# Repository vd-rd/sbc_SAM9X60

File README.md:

# Microchip SAM9X60 SBC

This board embeds a SIP (single core 600MHz ARM926 with 1Gb DDR2) with ACT8945a PMIC, IO headers and microSD/eMMC storage.

Board overview (draft):
[TBD]

## Board features
| Characteristic | Description |
| --- | --- |
| Dimensions | 60mm x 40mm |
| Processor | Microchip SAM9X60 @600MHz |
| Oscillators | 32.768kHz slow clock, 24MHz main clock |
| RAM | 128MB embedded DDR2 memory |
| Storage | microSD/eMMC |
| USB | 1 microUSB client |
| Ethernet | 2 10/100M RMII with pins on header |
| WiFi | 1 SDIO adapter with wifi/bt combo |
| Supply | Power path between USB/Vin/Battery, 5V max |

## Notes and observations
[TBD]

## Resources

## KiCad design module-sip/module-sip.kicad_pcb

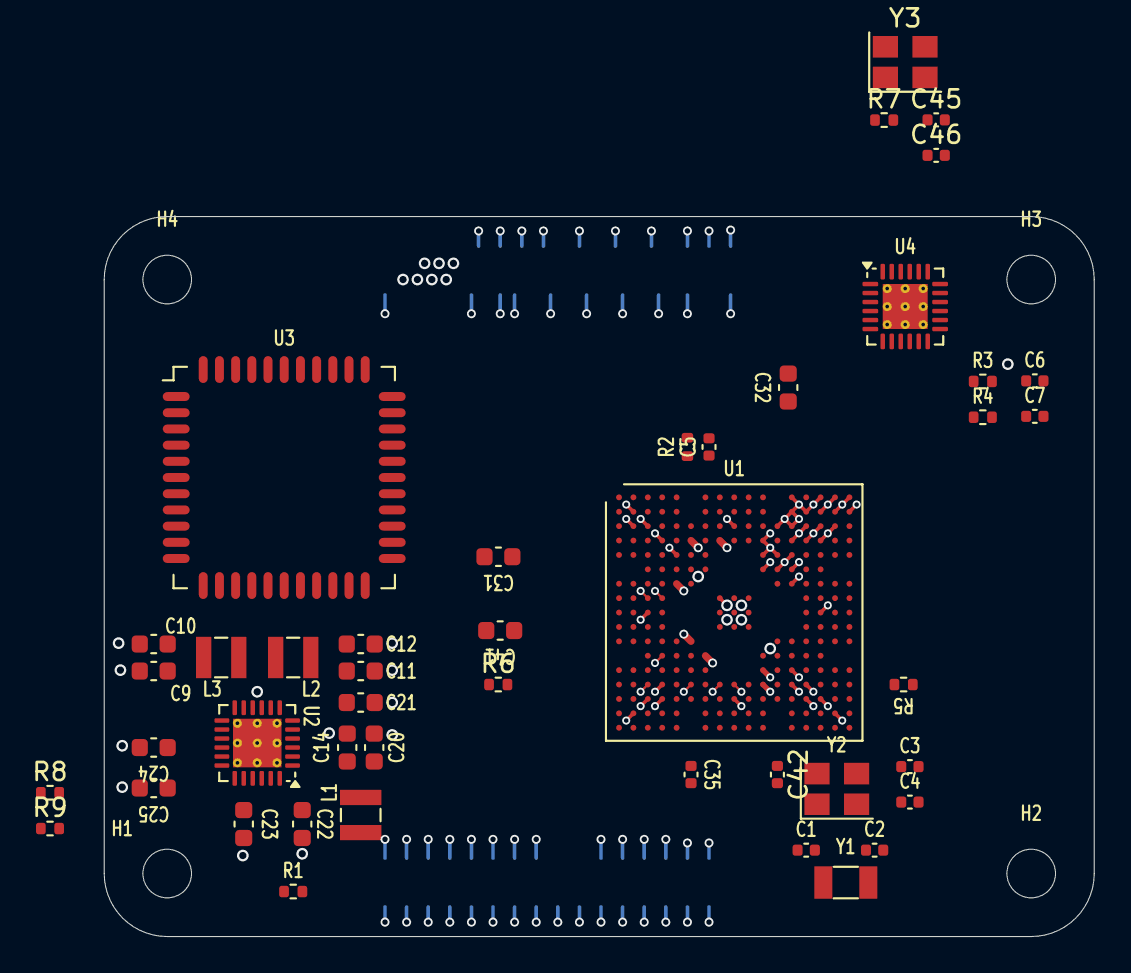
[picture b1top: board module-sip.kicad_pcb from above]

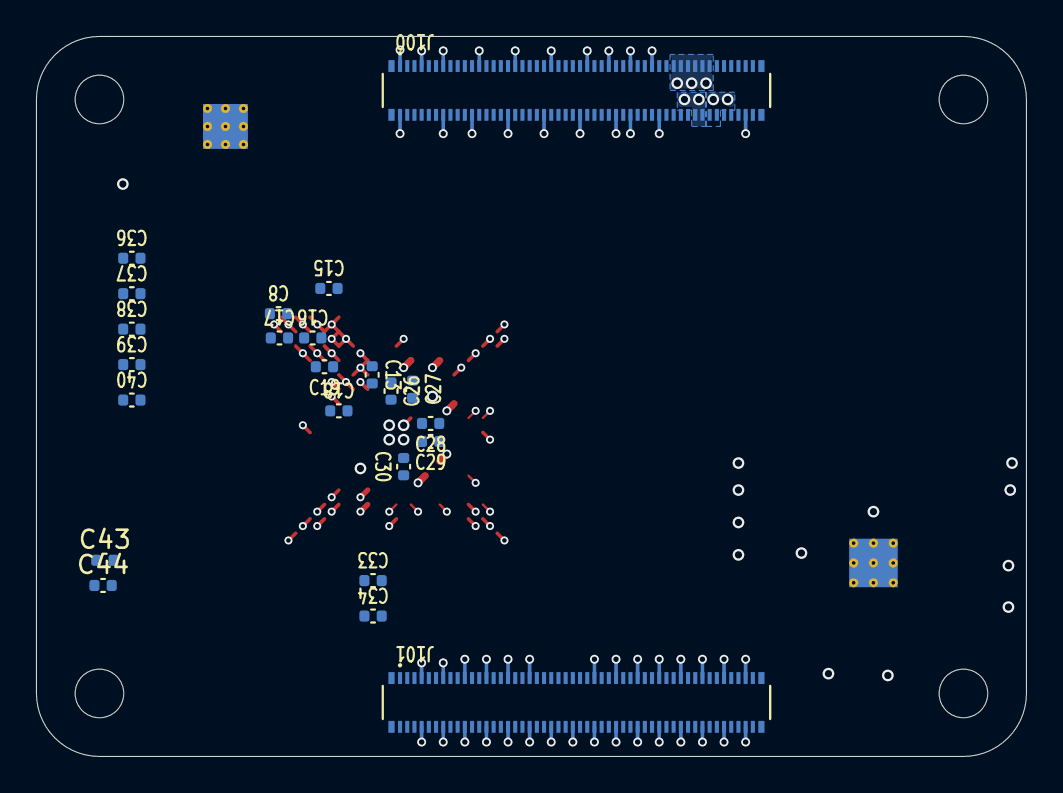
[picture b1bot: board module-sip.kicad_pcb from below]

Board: 4 copper layers, 55.0 x 40.0 mm, 71 parts (23 on the bottom side), 76 nets.

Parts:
C1, C2, C5: 9 pF; C_0402_1005Metric
C3, C4, C45, C46: 18 pF; C_0402_1005Metric
C6, C7, C8, C13, C15, C16, C17, C18, C19, C26, C27, C28, C29, C30, C33, C35, C36, C37, C38, C39, C40, C42, C43, C44: 100 nF; C_0402_1005Metric
C9, C10, C11, C12, C14, C20, C31, C32, C41: 10uF; C_0603_1608Metric
C21, C22, C23, C24, C25: 4.7uF; C_0603_1608Metric
C34: 2.2 uF; C_0402_1005Metric
H1, H2, H3, H4: MountingHole; MountingHole_2.7mm_M2.5_DIN965
J100, J101: DF40C-100DP-0.4V_51_; HRS_DF40C-100DP-0.4V_51_
L1, L2, L3: 2.2uH; L_Wuerth_MAPI-2510
R1, R3, R4, R8, R9: 10k; R_0402_1005Metric
R2: 20k; R_0402_1005Metric
R5: 5.62k; R_0402_1005Metric
R6: 0; R_0402_1005Metric
R7: 12k; R_0402_1005Metric
U1: SAM9X60D1G
U2: MCP16501; QFN-24-1EP_4x4mm_P0.5mm_EP2.7x2.7mm_ThermalVias
U3: AP6255; lga44_12x12mm_P0.9
U4: LAN8720A; VQFN-24-1EP_4x4mm_P0.5mm_EP2.5x2.5mm_ThermalVias
Y1: 32.768 kHz; Crystal_SMD_3215-2Pin_3.2x1.5mm
Y2: 24 MHz; Crystal_SMD_3225-4Pin_3.2x2.5mm
Y3: 25 MHz; Crystal_SMD_3225-4Pin_3.2x2.5mm

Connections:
+3V3: C14.1, C20.1, C36.1, C37.1, C38.1, C39.1, C40.1, C41.1, J100.84, J100.86, L1.2, R1.1, R6.1, U1.F5 (VDDIOP0), U1.K4 (VDDIOP0), U1.L4 (VDDIOP0), U1.M3 (VDDIOP1), U1.M15 (VDDNF), U2.1 (OUT1)
+5V: C21.1, C22.1, C23.1, C24.1, J100.77, J100.79, J100.81, J100.83, J100.85, J100.87, U2.7 (PVIN2), U2.12 (PVIN3), U2.17 (VIN), U2.20 (SELv2), U2.24 (PVIN1)
/cm-conns/+1.8v: J100.88, J100.90
/cpu/+3v3_ana: C42.1, C43.1, C44.1, R6.2, U1.C2 (VDDANA), U1.N11 (VDDIN33), U1.R12 (VDDIN33)
/cpu/ddr_cal: C5.1, R2.1, U1.C8 (DDR_CAL)
/cpu/ddr_vref: C6.1, C7.2, R3.1, R4.2, U1.A14 (DDR_VREF)
/cpu/hse_in: C3.1, U1.T11 (XIN), Y2.4
/cpu/hse_out: C4.1, U1.U11 (XOUT), Y2.2
/cpu/lse_in: C1.1, U1.U10 (XIN32), Y1.2
/cpu/lse_out: C2.1, U1.T10 (XOUT32), Y1.1
/networking/clk_in: C45.1, U4.5 (XTAL1/CLKIN), Y3.4
/networking/clk_out: C46.1, U4.4 (XTAL2), Y3.2
DBG-RXD: J100.51, U1.N2 (PA9)
DBG-TXD: J100.55, U1.M4 (PA10)
ETH_LEDG: J100.17, U4.3 (LED1/REGOFF)
ETH_LEDY: J100.15, U4.2 (LED2/~INTSEL)
GND: C1.2, C2.2, C3.2, C4.2, C5.2, C6.2, C8.2, C9.2, C10.2, C11.2, C12.2, C13.2, C14.2, C15.2, C16.2, C17.2, C18.2, C19.2, C20.2, C21.2, C22.2, C23.2, C24.2, C25.2, C26.2, C27.2, C28.2, C29.2, C30.2, C31.2, C32.2, C33.2, C34.2, C35.2, C36.2, C37.2, C38.2, C39.2, C40.2, C41.2, C42.2, C43.2, C44.2, C45.2, C46.2, J100.1, J100.2, J100.7, J100.8, J100.13, J100.14, J100.22, J100.23, J100.32, J100.33, J100.42, J100.43, J100.52, J100.53, J100.59, J100.60, J100.65, J100.66, J100.71, J100.74, J100.98, J101.7, J101.8, J101.13, J101.14, J101.19, J101.20, J101.25, J101.26, J101.31, J101.32, J101.37, J101.38, J101.44, J101.50, J101.55, J101.56, J101.61, J101.62, J101.67, J101.68, J101.73, J101.74, J101.79, J101.80, J101.85, J101.86, J101.91, J101.92, J101.97, J101.98, R2.2, R3.2, R5.1, R9.2, U1.C1 (ADVREFN), U1.C3 (GNDANA), U1.G (GND), U1.N7 (GNDIN33), U1.N14 (JTAGSEL), U1.P7 (GNDIN33), U2.9 (PGND2), U2.10 (PGND3), U2.16 (SGND), U2.22 (PGND1), U2.25 (EP), U4.25 (VSS), Y2.1, Y2.3, Y3.1, Y3.3
I2C-SCL: J100.80, U1.L3 (PA1)
I2C-SDA: J100.82, U1.L2 (PA0)
LCD02: J101.90, U1.T4 (PC2)
LCD03: J101.88, U1.T1 (PC3)
LCD04: J101.84, U1.R5 (PC4)
LCD05: J101.82, U1.U4 (PC5)
LCD06: J101.78, U1.T7 (PC6)
LCD07: J101.76, U1.R2 (PC7)
LCD10: J101.72, U1.T8 (PC10)
LCD11: J101.70, U1.T3 (PC11)
LCD12: J101.66, U1.T5 (PC12)
LCD13: J101.64, U1.R4 (PC13)
LCD14: J101.60, U1.U2 (PC14)
LCD15: J101.58, U1.U5 (PC15)
LCD18: J101.54, U1.R7 (PC18)
LCD19: J101.52, U1.P6 (PC19)
LCD20: J101.48, U1.T14 (PC20)
LCD21: J101.46, U1.P8 (PC21)
LCD22: J101.45, U1.R14 (PC22)
LCD23: J101.43, U1.T9 (PC23)
LCD_CLK: J101.47, U1.T13 (PC30)
LCD_DE: J101.49, U1.P9 (PC29)
LCD_HSYNC: J101.51, U1.P13 (PC28)
LCD_VSYNC: J101.53, U1.U9 (PC27)
unnamed: R5.2, U1.P17 (RTUNE)
unnamed: R8.2, R9.1, U2.19 (LFB)
unnamed: C25.1, R8.1, U2.18 (LOUT)
unnamed: L1.1, U2.23 (SW1)
unnamed: L2.1, U2.8 (SW2)
unnamed: L3.1, U2.11 (SW3)
unnamed: U3.1 (GND), U3.3 (GND), U3.20 (GND), U3.31 (GND), U3.33 (GND), U3.36 (GND)
unnamed: R7.1, U4.24 (RBIAS)
RMII_CRS: U1.D2 (PB3), U4.11 (CRS_DV/MODE2)
RMII_MDC: U1.D3 (PB6), U4.13 (MDC)
RMII_MDIO: U1.E1 (PB5), U4.12 (MDIO)
RMII_RX0: U1.B3 (PB0), U4.8 (RXD0/MODE0)
RMII_RX1: U1.D1 (PB1), U4.7 (RXD1/MODE1)
RMII_RXER: U1.A3 (PB2), U4.10 (RXER/PHYAD0)
RMII_TX0: U1.B4 (PB9), U4.17 (TXD0)
RMII_TX1: U1.B5 (PB10), U4.18 (TXD1)
RMII_TXEN: U1.F4 (PB7), U4.16 (TXEN)
SDIO0-CLK: J100.57, U1.J2 (PA16)
SDIO0-CMD: J100.62, U1.H4 (PA17)
SDIO0-DAT0: J100.63, U1.K1 (PA15)
SDIO0-DAT1: J100.67, U1.H3 (PA18)
SDIO0-DAT2: J100.69, U1.J1 (PA19)
SDIO0-DAT3: J100.61, U1.J4 (PA20)
TRD0_N: J100.10, U4.20 (TXN)
TRD0_P: J100.12, U4.21 (TXP)
TRD1_N: J100.6, U4.22 (RXN)
TRD1_P: J100.4, U4.23 (RXP)
UART0-RXD: J100.34, U1.P2 (PA7)
UART0-TXD: J100.54, U1.P3 (PA8)
VDDBU: C35.1, U1.R6 (VDDBU)
VDDOUT25: C33.1, C34.1, U1.P11 (VDDOUT25)
VDD_CORE: C9.1, C10.1, C26.1, C27.1, C28.1, C29.1, C30.1, C31.1, L3.2, U1.D6 (VDDCORE), U1.D8 (VDDCORE), U1.G5 (VDDCORE), U1.L6 (VDDCORE), U1.M7 (VDDCORE), U2.13 (OUT3)
VDD_DDR: C7.1, C8.1, C13.1, C15.1, C16.1, C17.1, C18.1, C19.1, C32.1, R4.1, U1.A16 (DDRM_VDD), U1.B15 (DDRM_VDD), U1.B17 (DDRM_VDD), U1.C14 (DDRM_VDD), U1.C16 (DDRM_VDD), U1.D11 (VDDIOM), U1.D13 (DDRM_VDD), U1.D15 (DDRM_VDD), U1.E11 (DDRM_VDD), U1.E12 (DDRM_VDD), U1.E14 (VDDIOM), U1.F13 (DDRM_VDD), U1.G13 (DDRM_VDD), U1.G14 (VDDIOM)
VDD_RAM: C11.1, C12.1, L2.2, U2.6 (OUT2)
nRST: J100.100, R1.2, U1.P1 (NRST), U2.2 (~RSTO)

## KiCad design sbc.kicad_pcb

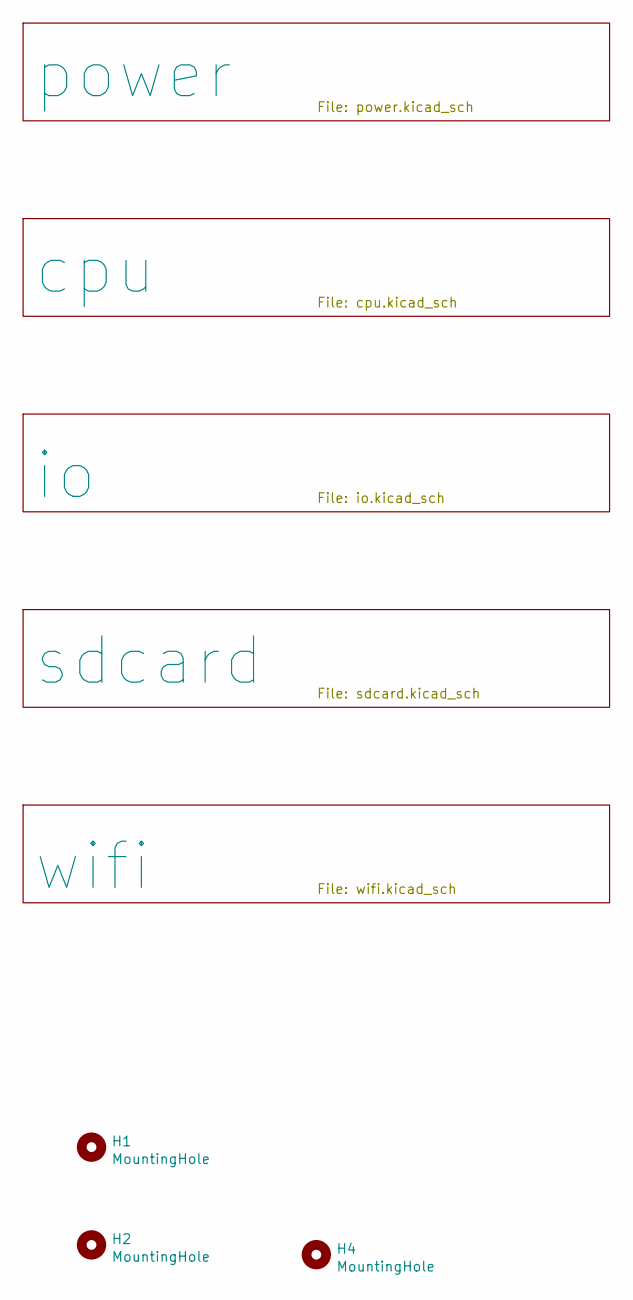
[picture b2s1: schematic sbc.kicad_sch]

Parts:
H1, H2, H4: MountingHole; MountingHole_2.7mm_M2.5_DIN965

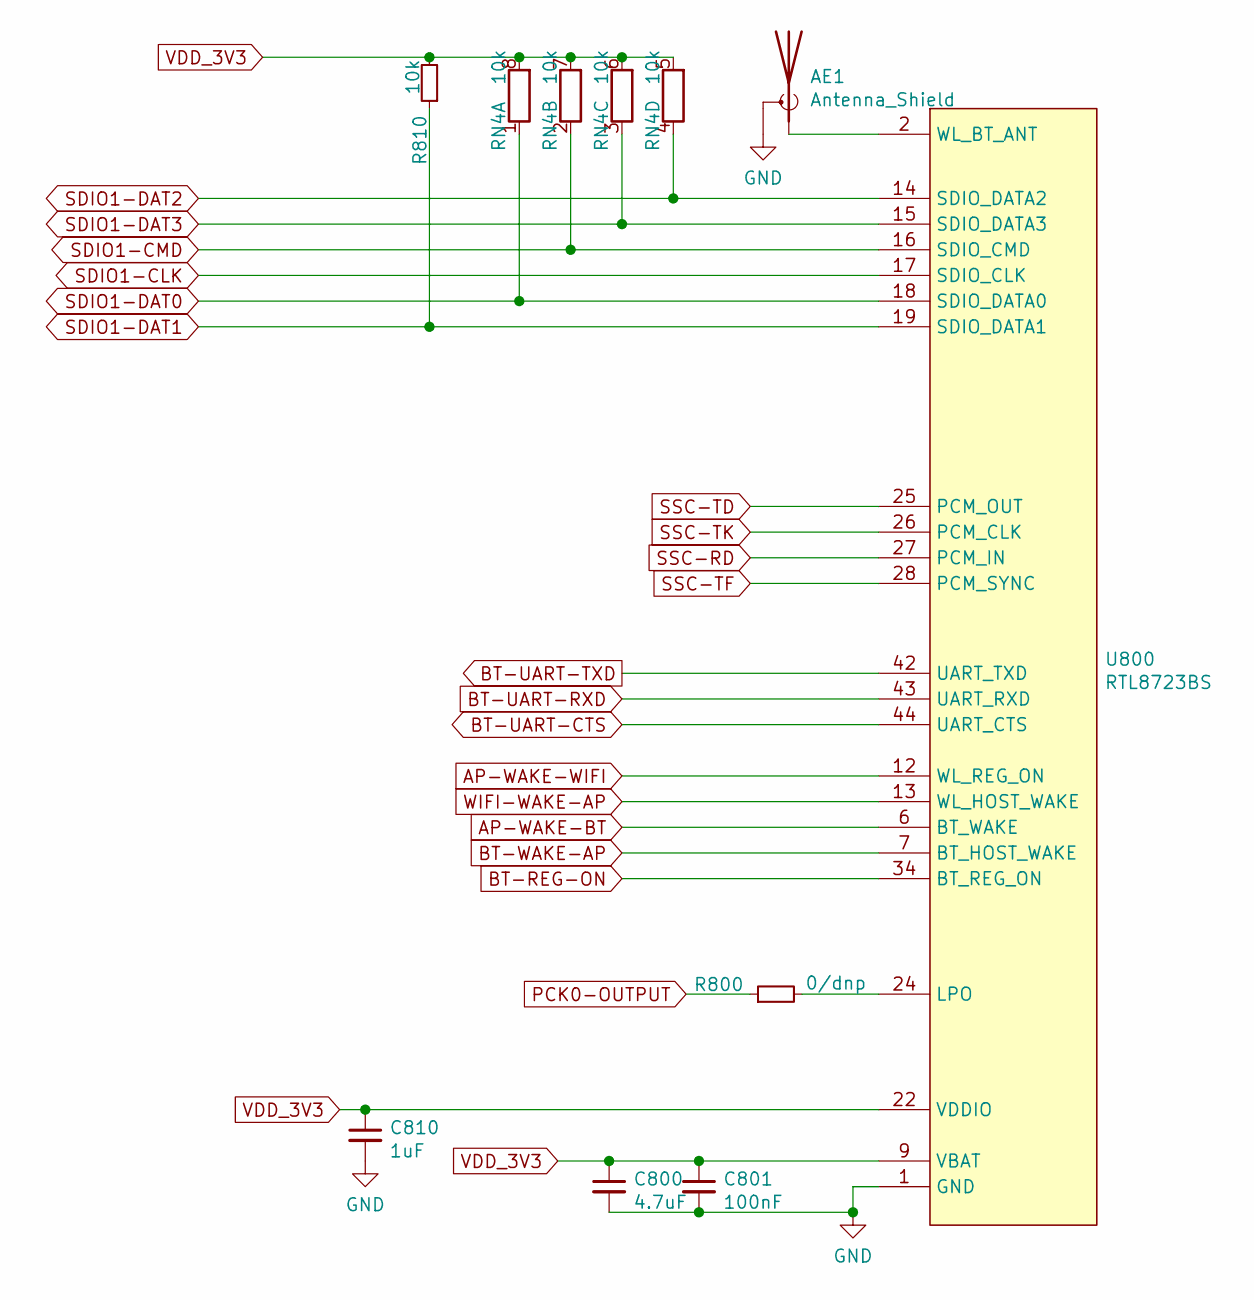
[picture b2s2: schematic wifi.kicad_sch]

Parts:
AE1: Antenna_Shield; U.FL_Hirose_U.FL-R-SMT-1_Vertical
C800: 4.7uF; C_0603_1608Metric
C801: 100nF; C_0402_1005Metric
C810: 1uF; C_0402_1005Metric
R800: 0/dnp; R_0402_1005Metric
R810: 10k; R_0402_1005Metric
RN4: 10k; R_Array_Convex_4x0402
U800: RTL8723BS; lga44_12x12mm_P0.9

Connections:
AP-WAKE-BT: U800.6 (BT_WAKE); also elsewhere on the board
AP-WAKE-WIFI: U800.12 (WL_REG_ON); also elsewhere on the board
BT-REG-ON: U800.34 (BT_REG_ON); also elsewhere on the board
BT-UART-CTS: U800.44 (UART_CTS)
BT-UART-RXD: U800.43 (UART_RXD)
BT-UART-TXD: U800.42 (UART_TXD)
BT-WAKE-AP: U800.7 (BT_HOST_WAKE); also elsewhere on the board
GND: AE1.2 (Shield), C800.2, C801.2, C810.2, U800.1 (GND), U800.3 (GND), U800.20 (GND), U800.31 (GND), U800.33 (GND), U800.36 (GND), U800.41 (GND); also elsewhere on the board
unnamed: AE1.1 (A), U800.2 (WL_BT_ANT)
unnamed: R800.2, U800.24 (LPO)
PCK0-OUTPUT: R800.1; also elsewhere on the board
SDIO1-CLK: U800.17 (SDIO_CLK); also elsewhere on the board
SDIO1-CMD: RN4.2 (R2.1), U800.16 (SDIO_CMD); also elsewhere on the board
SDIO1-DAT0: RN4.1 (R1.1), U800.18 (SDIO_DATA0); also elsewhere on the board
SDIO1-DAT1: R810.1, U800.19 (SDIO_DATA1); also elsewhere on the board
SDIO1-DAT2: RN4.4 (R4.1), U800.14 (SDIO_DATA2); also elsewhere on the board
SDIO1-DAT3: RN4.3 (R3.1), U800.15 (SDIO_DATA3); also elsewhere on the board
SSC-RD: U800.27 (PCM_IN); also elsewhere on the board
SSC-TD: U800.25 (PCM_OUT); also elsewhere on the board
SSC-TF: U800.28 (PCM_SYNC); also elsewhere on the board
SSC-TK: U800.26 (PCM_CLK); also elsewhere on the board
VDD_3V3: C800.1, C801.1, C810.1, R810.2, RN4.5 (R4.2), RN4.6 (R3.2), RN4.7 (R2.2), RN4.8 (R1.2), U800.9 (VBAT), U800.22 (VDDIO); also elsewhere on the board
WIFI-WAKE-AP: U800.13 (WL_HOST_WAKE)

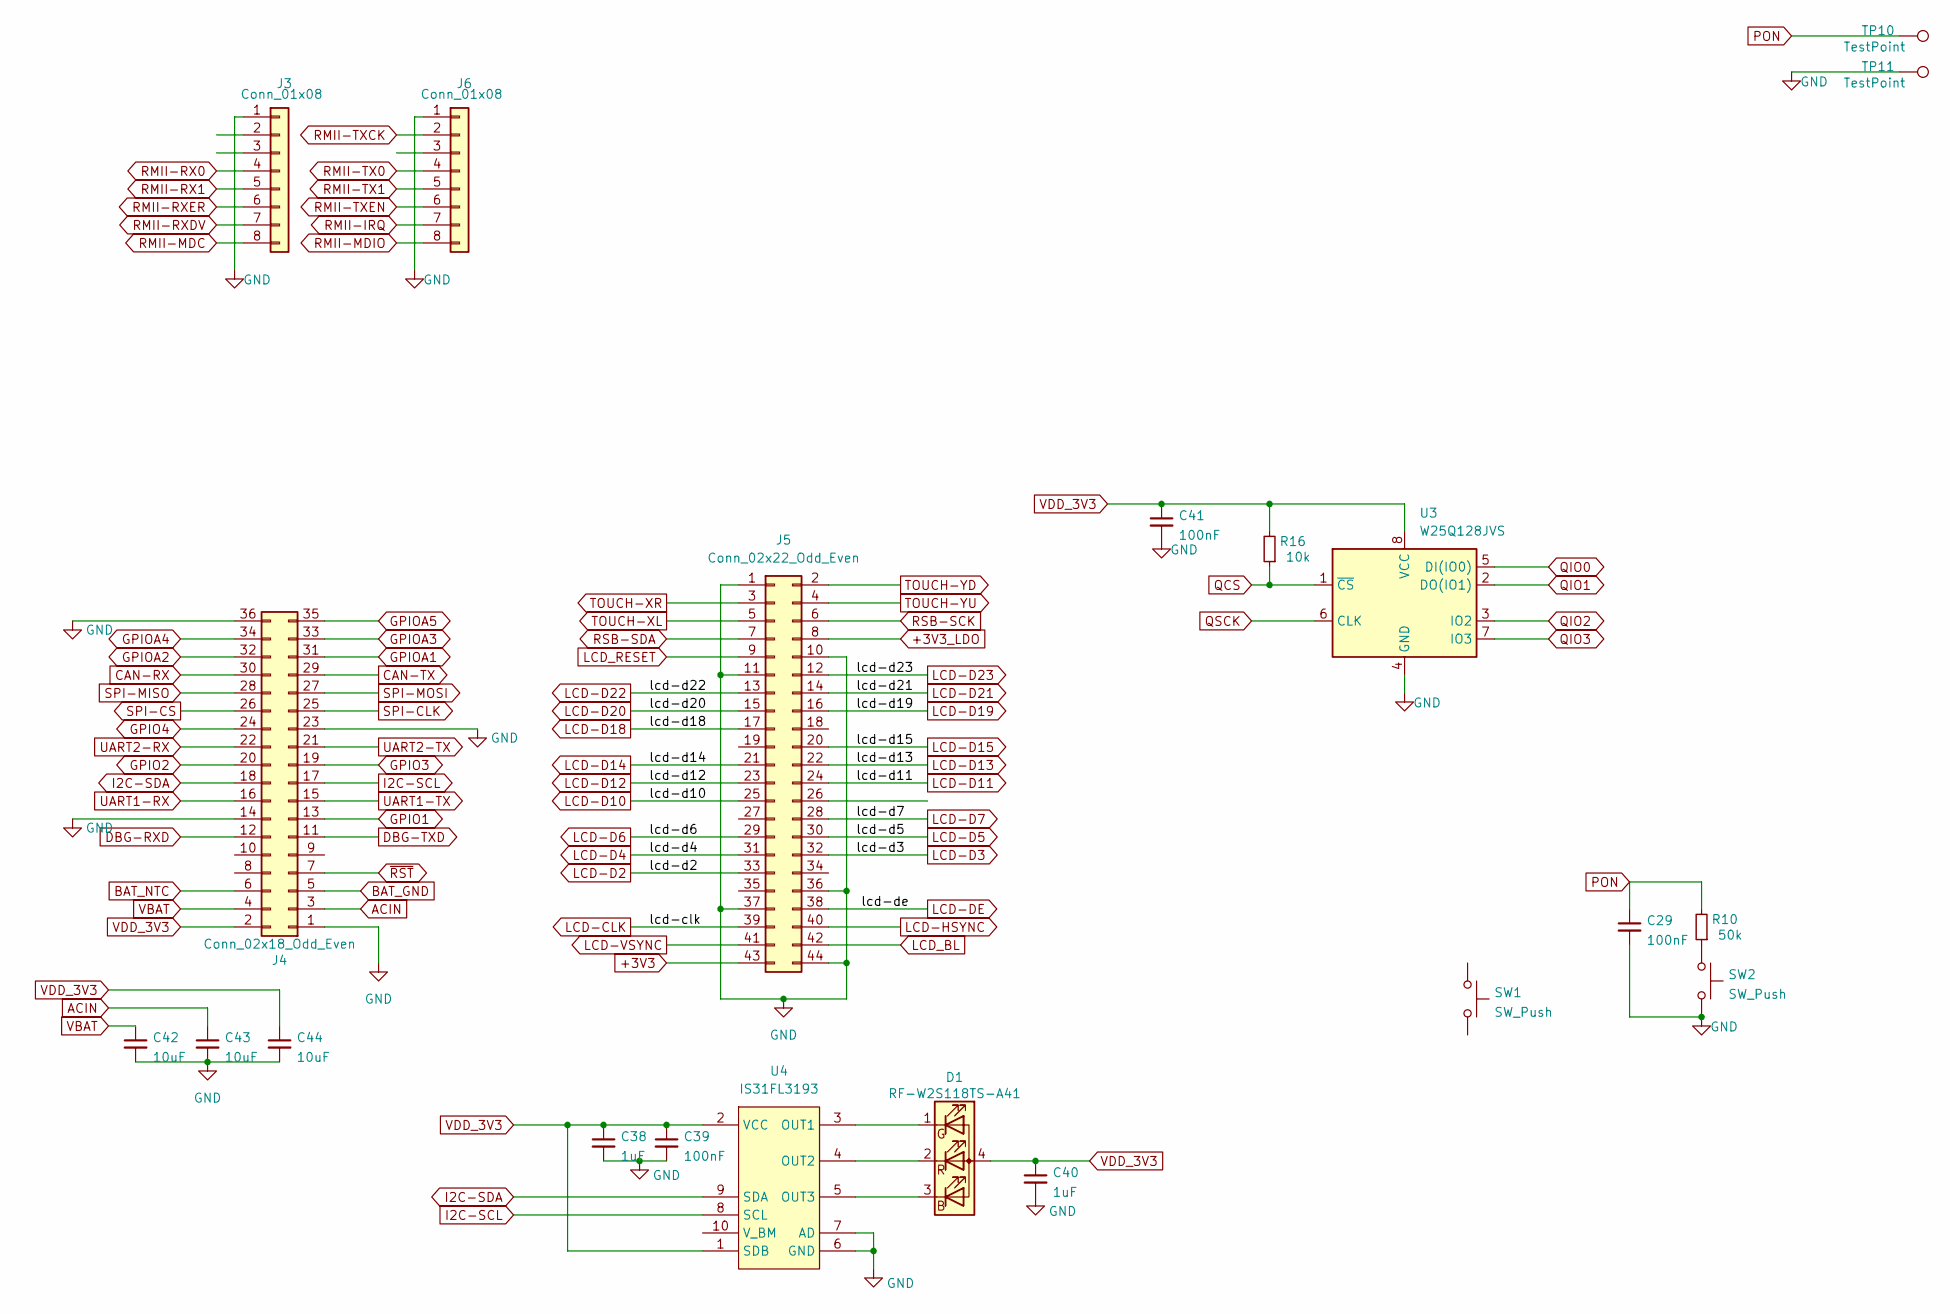
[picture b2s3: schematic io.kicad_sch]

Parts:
C29, C39, C41: 100nF; C_0402_1005Metric
C38, C40: 1uF; C_0402_1005Metric
C42, C43, C44: 10uF; C_0805_2012Metric
D1: RF-W2S118TS-A41; rgb-1204
J3, J6: Conn_01x08; PinHeader_2x04_P1.27mm_Vertical
J4: Conn_02x18_Odd_Even; PinHeader_2x18_P2.54mm_Vertical
J5: Conn_02x22_Odd_Even; PinHeader_2x22_P1.27mm_Vertical
R10: 50k; R_0402_1005Metric
R16: 10k; R_0402_1005Metric
SW1, SW2: SW_Push; SW_SPST_EVQP7C
TP10, TP11: TestPoint; TestPoint_Pad_D1.0mm
U3: W25Q128JVS; SOIC-8_5.23x5.23mm_P1.27mm
U4: IS31FL3193; DFN-10-1EP_3x3mm_P0.5mm_EP1.7x2.5mm

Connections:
+3V3: J5.43
+3V3_LDO: J5.8
ACIN: C43.1, J4.3; also elsewhere on the board
BAT_GND: J4.5; also elsewhere on the board
BAT_NTC: J4.6; also elsewhere on the board
CAN-RX: J4.30; also elsewhere on the board
CAN-TX: J4.29; also elsewhere on the board
DBG-RXD: J4.12; also elsewhere on the board
DBG-TXD: J4.11; also elsewhere on the board
GND: C29.2, C38.2, C39.2, C40.2, C41.2, C42.2, C43.2, C44.2, J3.1, J4.1, J4.14, J4.23, J4.36, J5.1, J5.10, J5.11, J5.18, J5.19, J5.26, J5.27, J5.34, J5.35, J5.36, J5.37, J5.44, J6.1, SW2.2, TP11.1, U3.4 (GND), U4.6 (GND), U4.7 (AD), U4.11 (GND); also elsewhere on the board
GPIO1: J4.13; also elsewhere on the board
GPIO2: J4.20; also elsewhere on the board
GPIO3: J4.19; also elsewhere on the board
GPIO4: J4.24; also elsewhere on the board
GPIOA1: J4.31
GPIOA2: J4.32; also elsewhere on the board
GPIOA3: J4.33; also elsewhere on the board
GPIOA4: J4.34; also elsewhere on the board
GPIOA5: J4.35; also elsewhere on the board
I2C-SCL: J4.17, U4.8 (SCL); also elsewhere on the board
I2C-SDA: J4.18, U4.9 (SDA); also elsewhere on the board
LCD-CLK: J5.39; also elsewhere on the board
LCD-D2: J5.33; also elsewhere on the board
LCD-D3: J5.32; also elsewhere on the board
LCD-D4: J5.31; also elsewhere on the board
LCD-D5: J5.30; also elsewhere on the board
LCD-D6: J5.29; also elsewhere on the board
LCD-D7: J5.28; also elsewhere on the board
LCD-D10: J5.25; also elsewhere on the board
LCD-D11: J5.24; also elsewhere on the board
LCD-D12: J5.23; also elsewhere on the board
LCD-D13: J5.22; also elsewhere on the board
LCD-D14: J5.21; also elsewhere on the board
LCD-D15: J5.20; also elsewhere on the board
LCD-D18: J5.17; also elsewhere on the board
LCD-D19: J5.16; also elsewhere on the board
LCD-D20: J5.15; also elsewhere on the board
LCD-D21: J5.14; also elsewhere on the board
LCD-D22: J5.13; also elsewhere on the board
LCD-D23: J5.12; also elsewhere on the board
LCD-DE: J5.38; also elsewhere on the board
LCD-HSYNC: J5.40; also elsewhere on the board
LCD-VSYNC: J5.41; also elsewhere on the board
LCD_BL: J5.42
LCD_RESET: J5.9
unnamed: D1.1 (GK), U4.3 (OUT1)
unnamed: D1.2 (RK), U4.4 (OUT2)
unnamed: D1.3 (BK), U4.5 (OUT3)
unnamed: R10.1, SW2.1
PON: C29.1, R10.2, TP10.1; also elsewhere on the board
QCS: R16.1, U3.1 (~CS); also elsewhere on the board
QIO0: U3.5 (DI(IO0)); also elsewhere on the board
QIO1: U3.2 (DO(IO1)); also elsewhere on the board
QIO2: U3.3 (IO2); also elsewhere on the board
QIO3: U3.7 (IO3); also elsewhere on the board
QSCK: U3.6 (CLK); also elsewhere on the board
RMII-IRQ: J6.7; also elsewhere on the board
RMII-MDC: J3.8; also elsewhere on the board
RMII-MDIO: J6.8; also elsewhere on the board
RMII-RX0: J3.4; also elsewhere on the board
RMII-RX1: J3.5; also elsewhere on the board
RMII-RXDV: J3.7; also elsewhere on the board
RMII-RXER: J3.6; also elsewhere on the board
RMII-TX0: J6.4; also elsewhere on the board
RMII-TX1: J6.5; also elsewhere on the board
RMII-TXCK: J6.2; also elsewhere on the board
RMII-TXEN: J6.6; also elsewhere on the board
RSB-SCK: J5.6
RSB-SDA: J5.7
SPI-CLK: J4.25; also elsewhere on the board
SPI-CS: J4.26; also elsewhere on the board
SPI-MISO: J4.28; also elsewhere on the board
SPI-MOSI: J4.27; also elsewhere on the board
TOUCH-XL: J5.5
TOUCH-XR: J5.3
TOUCH-YD: J5.2
TOUCH-YU: J5.4
UART1-RX: J4.16
UART1-TX: J4.15
UART2-RX: J4.22
UART2-TX: J4.21
VBAT: C42.1, J4.4; also elsewhere on the board
VDD_3V3: C38.1, C39.1, C40.1, C41.1, C44.1, D1.4 (A), J4.2, R16.2, U3.8 (VCC), U4.1 (SDB), U4.2 (VCC); also elsewhere on the board
~RST: J4.7; also elsewhere on the board

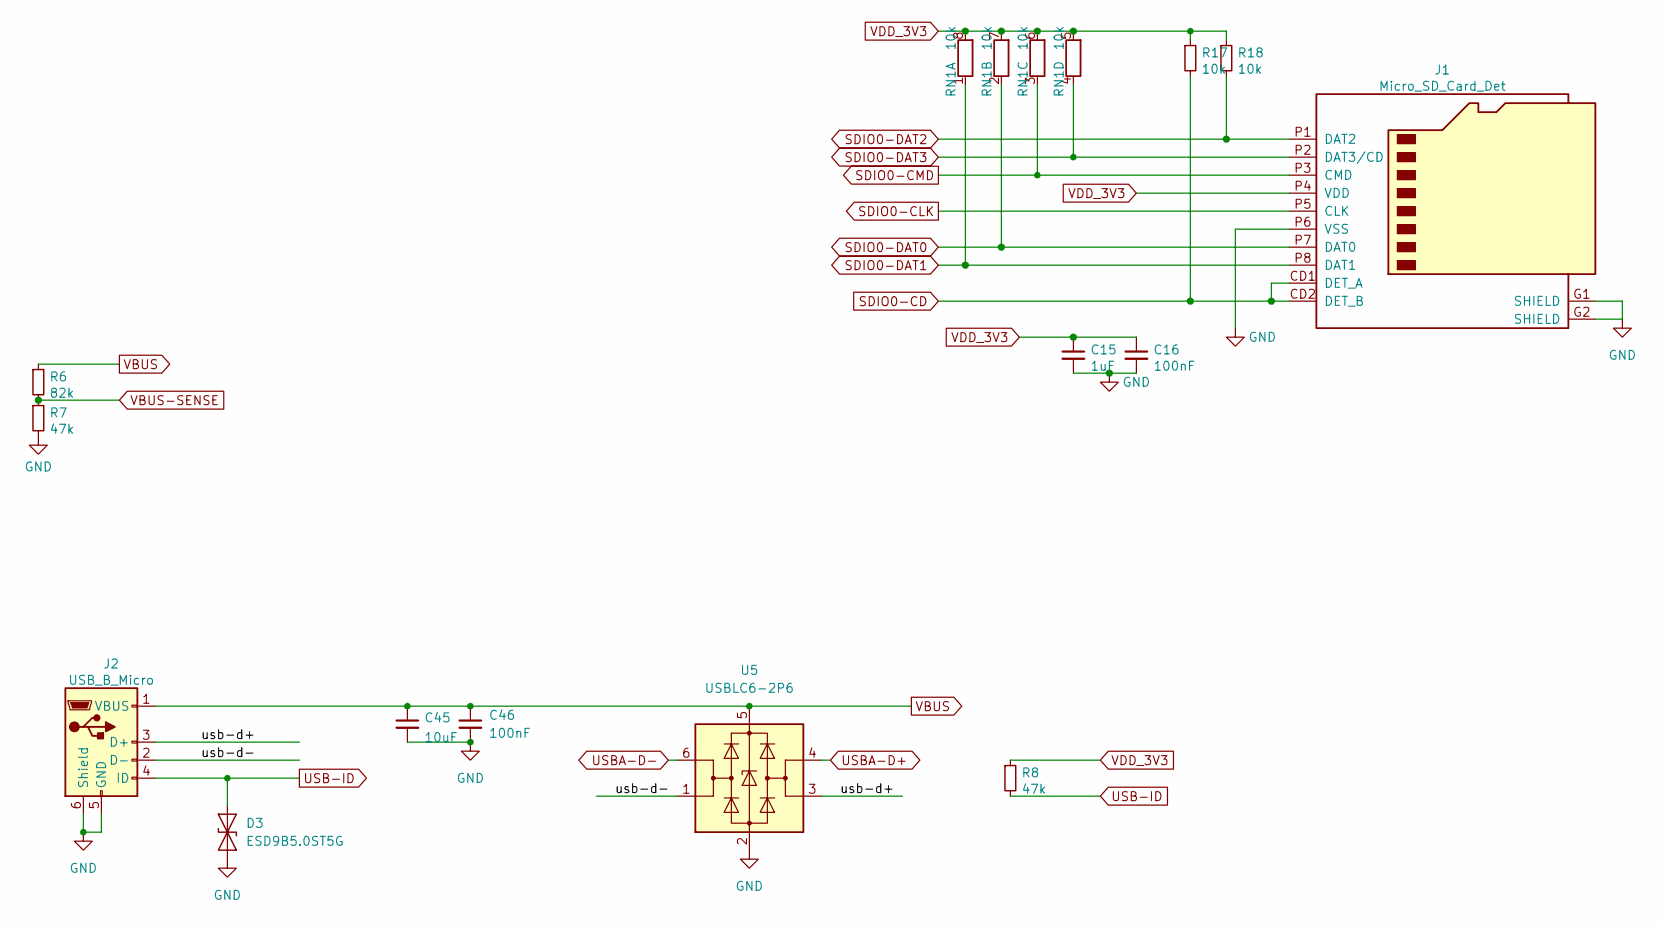
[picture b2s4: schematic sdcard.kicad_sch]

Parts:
C15: 1uF; C_0402_1005Metric
C16, C46: 100nF; C_0402_1005Metric
C45: 10uF; C_0805_2012Metric
D3: ESD9B5.0ST5G; D_SOD-923
J1: Micro_SD_Card_Det; MEM20610118800A
J2: USB_B_Micro; USB_Micro-B_Amphenol_10103594-0001LF_Horizontal
R6: 82k; R_0402_1005Metric
R7, R8: 47k; R_0402_1005Metric
R17, R18: 10k; R_0402_1005Metric
RN1: 10k; R_Array_Convex_4x0402
U5: USBLC6-2P6; SOT-666

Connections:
/sdcard/usb-d+: J2.3 (D+), U5.3 (I/O2)
/sdcard/usb-d-: J2.2 (D-), U5.1 (I/O1)
GND: C15.2, C16.2, C45.2, C46.2, D3.2 (A2), J1.G1 (SHIELD), J1.G2 (SHIELD), J1.P6 (VSS), J2.5 (GND), J2.6 (Shield), R7.2, U5.2 (GND); also elsewhere on the board
SDIO0-CD: J1.CD1 (DET_A), J1.CD2 (DET_B), R17.2; also elsewhere on the board
SDIO0-CLK: J1.P5 (CLK); also elsewhere on the board
SDIO0-CMD: J1.P3 (CMD), RN1.3 (R3.1); also elsewhere on the board
SDIO0-DAT0: J1.P7 (DAT0), RN1.2 (R2.1); also elsewhere on the board
SDIO0-DAT1: J1.P8 (DAT1), RN1.1 (R1.1); also elsewhere on the board
SDIO0-DAT2: J1.P1 (DAT2), R18.2; also elsewhere on the board
SDIO0-DAT3: J1.P2 (DAT3/CD), RN1.4 (R4.1); also elsewhere on the board
USB-ID: D3.1 (A1), J2.4 (ID), R8.2
USBA-D+: U5.4 (I/O2); also elsewhere on the board
USBA-D-: U5.6 (I/O1); also elsewhere on the board
VBUS: C45.1, C46.1, J2.1 (VBUS), R6.1, U5.5 (VBUS); also elsewhere on the board
VBUS-SENSE: R6.2, R7.1
VDD_3V3: C15.1, C16.1, J1.P4 (VDD), R8.1, R17.1, R18.1, RN1.5 (R4.2), RN1.6 (R3.2), RN1.7 (R2.2), RN1.8 (R1.2); also elsewhere on the board

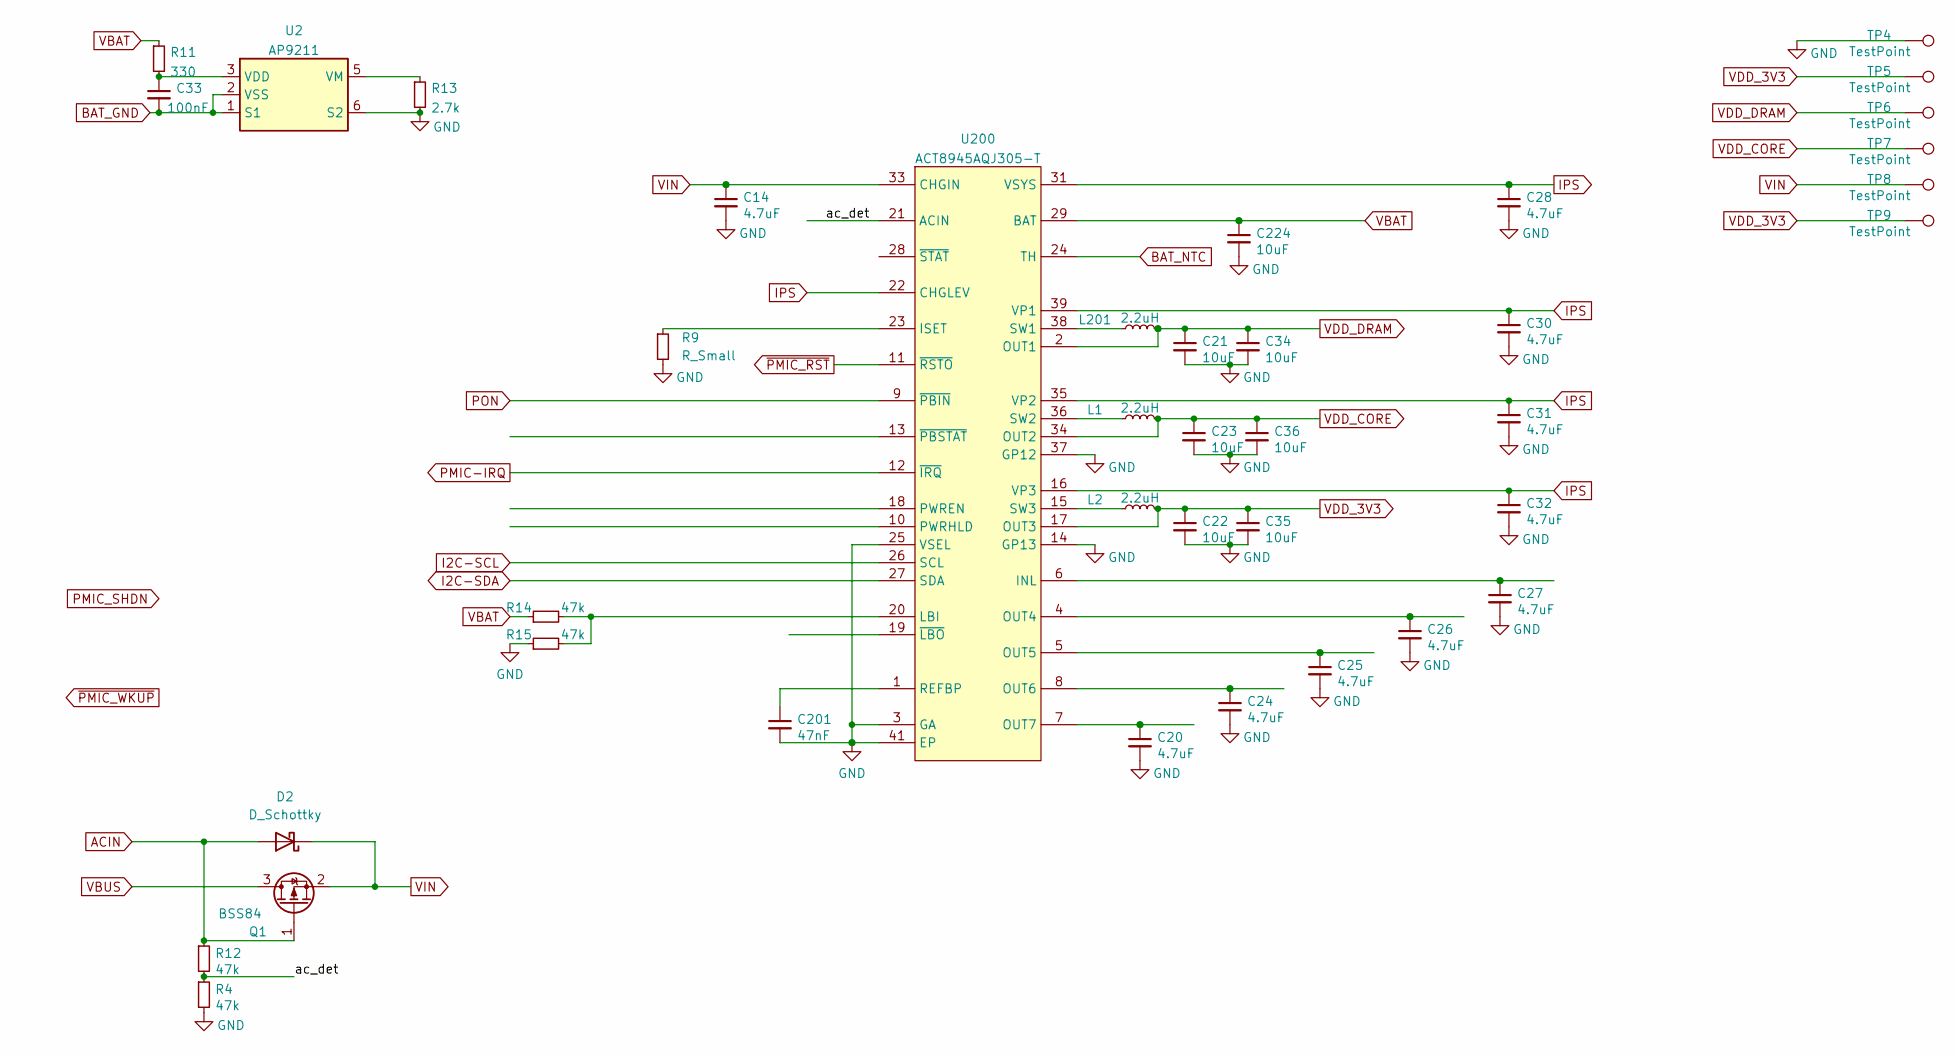
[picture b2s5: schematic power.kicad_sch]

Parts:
C14, C20, C24, C25, C26, C27, C28, C30, C31, C32: 4.7uF; C_0603_1608Metric
C21, C22, C23, C34, C35, C36, C224: 10uF; C_0603_1608Metric
C33: 100nF; C_0402_1005Metric
C201: 47nF; C_0402_1005Metric
D2: D_Schottky; D_SOD-323
L1, L2, L201: 2.2uH; L_Wuerth_MAPI-2510
Q1: BSS84; SOT-23
R4, R12, R14, R15: 47k; R_0402_1005Metric
R9: R_Small; R_0402_1005Metric
R11: 330; R_0402_1005Metric
R13: 2.7k; R_0402_1005Metric
TP4, TP5, TP6, TP7, TP8, TP9: TestPoint; TestPoint_Pad_D1.0mm
U2: AP9211; DFN-2030-6
U200: ACT8945AQJ305-T; TQFN-40-1EP_5x5mm_P0.4mm_EP3.5x3.5mm_ThermalVias

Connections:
/power/ac_det: R4.1, R12.2, U200.21 (ACIN)
ACIN: D2.2 (A), Q1.1 (G), R12.1; also elsewhere on the board
BAT_GND: C33.2, U2.1 (S1), U2.2 (VSS); also elsewhere on the board
BAT_NTC: U200.24 (TH); also elsewhere on the board
GND: C14.2, C20.2, C21.2, C22.2, C23.2, C24.2, C25.2, C26.2, C27.2, C28.2, C30.2, C31.2, C32.2, C34.2, C35.2, C36.2, C201.2, C224.2, R4.2, R9.2, R13.2, R15.1, TP4.1, U2.6 (S2), U200.3 (GA), U200.14 (GP13), U200.25 (VSEL), U200.37 (GP12), U200.41 (EP); also elsewhere on the board
I2C-SCL: U200.26 (SCL); also elsewhere on the board
I2C-SDA: U200.27 (SDA); also elsewhere on the board
IPS: C28.1, C30.1, C31.1, C32.1, U200.16 (VP3), U200.22 (CHGLEV), U200.31 (VSYS), U200.32 (VSYS), U200.35 (VP2), U200.39 (VP1)
unnamed: C20.1, U200.7 (OUT7)
unnamed: C24.1, U200.8 (OUT6)
unnamed: C25.1, U200.5 (OUT5)
unnamed: C26.1, U200.4 (OUT4)
unnamed: C27.1, U200.6 (INL)
unnamed: C33.1, R11.2, U2.3 (VDD)
unnamed: C201.1, U200.1 (REFBP)
unnamed: L1.1, U200.36 (SW2)
unnamed: L2.1, U200.15 (SW3)
unnamed: L201.1, U200.38 (SW1)
unnamed: R9.1, U200.23 (ISET)
unnamed: R13.1, U2.5 (VM)
unnamed: R14.2, R15.2, U200.20 (LBI)
PMIC-IRQ: U200.12 (~IRQ); also elsewhere on the board
PON: U200.9 (~PBIN); also elsewhere on the board
VBAT: C224.1, R11.1, R14.1, U200.29 (BAT), U200.30 (BAT); also elsewhere on the board
VBUS: Q1.3 (D); also elsewhere on the board
VDD_3V3: C22.1, C35.1, L2.2, TP5.1, TP9.1, U200.17 (OUT3); also elsewhere on the board
VDD_CORE: C23.1, C36.1, L1.2, TP7.1, U200.34 (OUT2); also elsewhere on the board
VDD_DRAM: C21.1, C34.1, L201.2, TP6.1, U200.2 (OUT1); also elsewhere on the board
VIN: C14.1, D2.1 (K), Q1.2 (S), TP8.1, U200.33 (CHGIN)
~PMIC_RST: U200.11 (~RSTO)
